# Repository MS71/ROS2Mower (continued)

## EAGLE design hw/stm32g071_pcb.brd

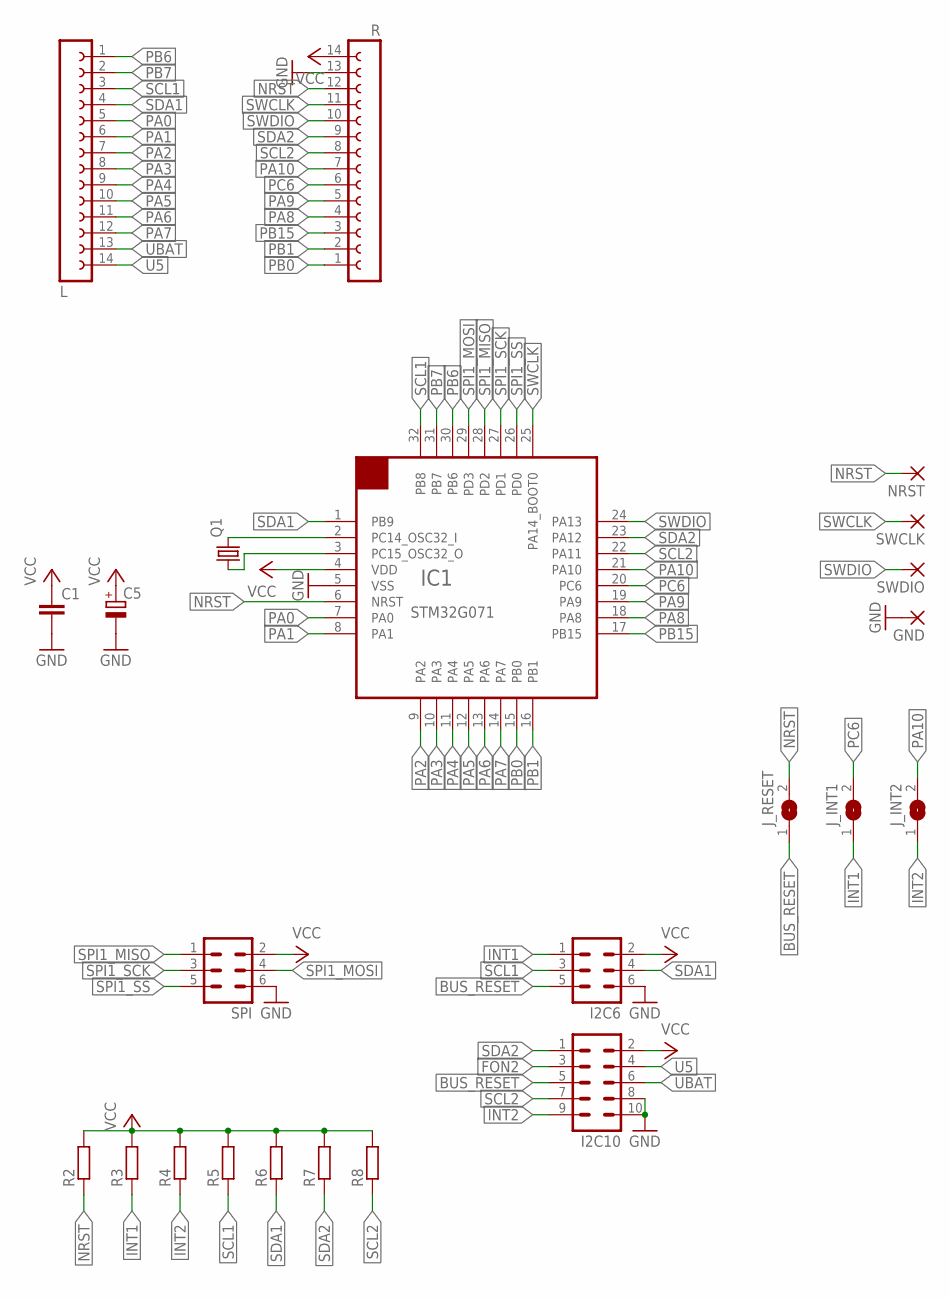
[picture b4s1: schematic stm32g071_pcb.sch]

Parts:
C1: C-EUC0805; C0805
C5: CPOL-EUB/3528-21W; B/3528-21W
GND: 1,6/0,8
I2C6: ML6
I2C10: ML10
IC1: STM32G071; LQFP-32
J_INT1, J_INT2: SJ
J_RESET: SJ
L: FE14-1; FE14
NRST: 1,6/0,8
Q1: CRYSTALTC26V; TC26V
R: FE14-1; FE14
R2, R3, R4, R5, R6, R7, R8: R-EU_R0805; R0805
SPI: ML6
SWCLK: 1,6/0,8
SWDIO: 1,6/0,8

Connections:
BUS_RESET: I2C6.5, I2C10.5, J_RESET.1
FON2: I2C10.3
GND: C1.2, C5.-, GND.1, I2C6.6, I2C10.8, I2C10.10, IC1.5 (VSS), R.13, SPI.6
INT1: I2C6.1, J_INT1.1, R3.1
INT2: I2C10.9, J_INT2.1, R4.1
unnamed: IC1.2 (PC14_OSC32_I), Q1.2
unnamed: IC1.3 (PC15_OSC32_O), Q1.1
NRST: IC1.6 (NRST), J_RESET.2, NRST.1, R.12, R2.1
PA0: IC1.7 (PA0), L.5
PA1: IC1.8 (PA1), L.6
PA2: IC1.9 (PA2), L.7
PA3: IC1.10 (PA3), L.8
PA4: IC1.11 (PA4), L.9
PA5: IC1.12 (PA5), L.10
PA6: IC1.13 (PA6), L.11
PA7: IC1.14 (PA7), L.12
PA8: IC1.18 (PA8), R.4
PA9: IC1.19 (PA9), R.5
PA10: IC1.21 (PA10), J_INT2.2, R.7
PB0: IC1.15 (PB0), R.1
PB1: IC1.16 (PB1), R.2
PB6: IC1.30 (PB6), L.1
PB7: IC1.31 (PB7), L.2
PB15: IC1.17 (PB15), R.3
PC6: IC1.20 (PC6), J_INT1.2, R.6
SCL1: I2C6.3, IC1.32 (PB8), L.3, R5.1
SCL2: I2C10.7, IC1.22 (PA11), R.8, R8.1
SDA1: I2C6.4, IC1.1 (PB9), L.4, R6.1
SDA2: I2C10.1, IC1.23 (PA12), R.9, R7.1
SPI1_MISO: IC1.28 (PD2), SPI.1
SPI1_MOSI: IC1.29 (PD3), SPI.4
SPI1_SCK: IC1.27 (PD1), SPI.3
SPI1_SS: IC1.26 (PD0), SPI.5
SWCLK: IC1.25 (PA14_BOOT0), R.11, SWCLK.1
SWDIO: IC1.24 (PA13), R.10, SWDIO.1
U5: I2C10.4, L.14
UBAT: I2C10.6, L.13
VCC: C1.1, C5.+, I2C6.2, I2C10.2, IC1.4 (VDD), R.14, R2.2, R3.2, R4.2, R5.2, R6.2, R7.2, R8.2, SPI.2

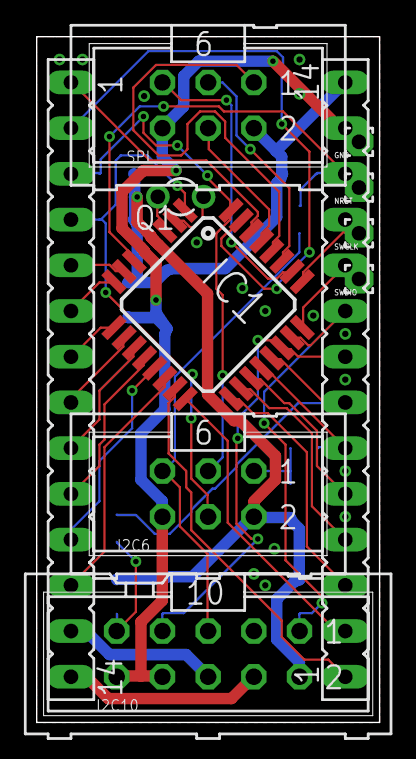
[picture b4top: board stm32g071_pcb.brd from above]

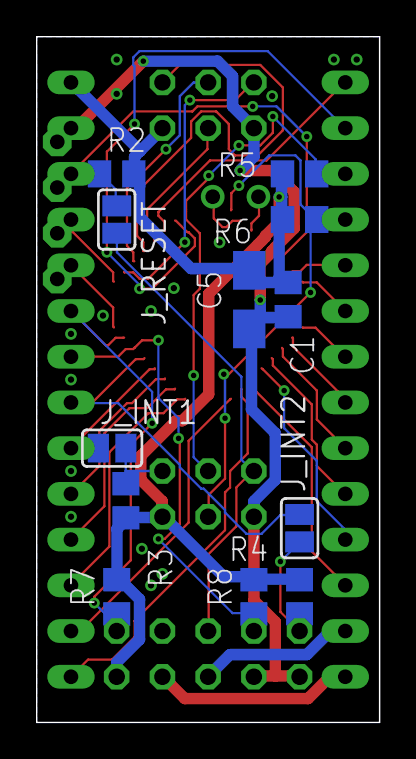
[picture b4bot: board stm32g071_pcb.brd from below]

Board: 2 copper layers, 19.1 x 38.1 mm, 23 parts (12 on the bottom side), 37 nets.
